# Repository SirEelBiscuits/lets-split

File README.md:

# lets-split

a custom remake of the lets split keyboard pcb

PCB designed to match [this case](https://mechboards.co.uk/shop/kits/lets-split-kit/#pcb).

Uses the QMK firmware, my fork of which is here: https://github.com/SirEelBiscuits/qmk_firmware/tree/garnet

As yet, keyboard and keymap are not merged upstream.

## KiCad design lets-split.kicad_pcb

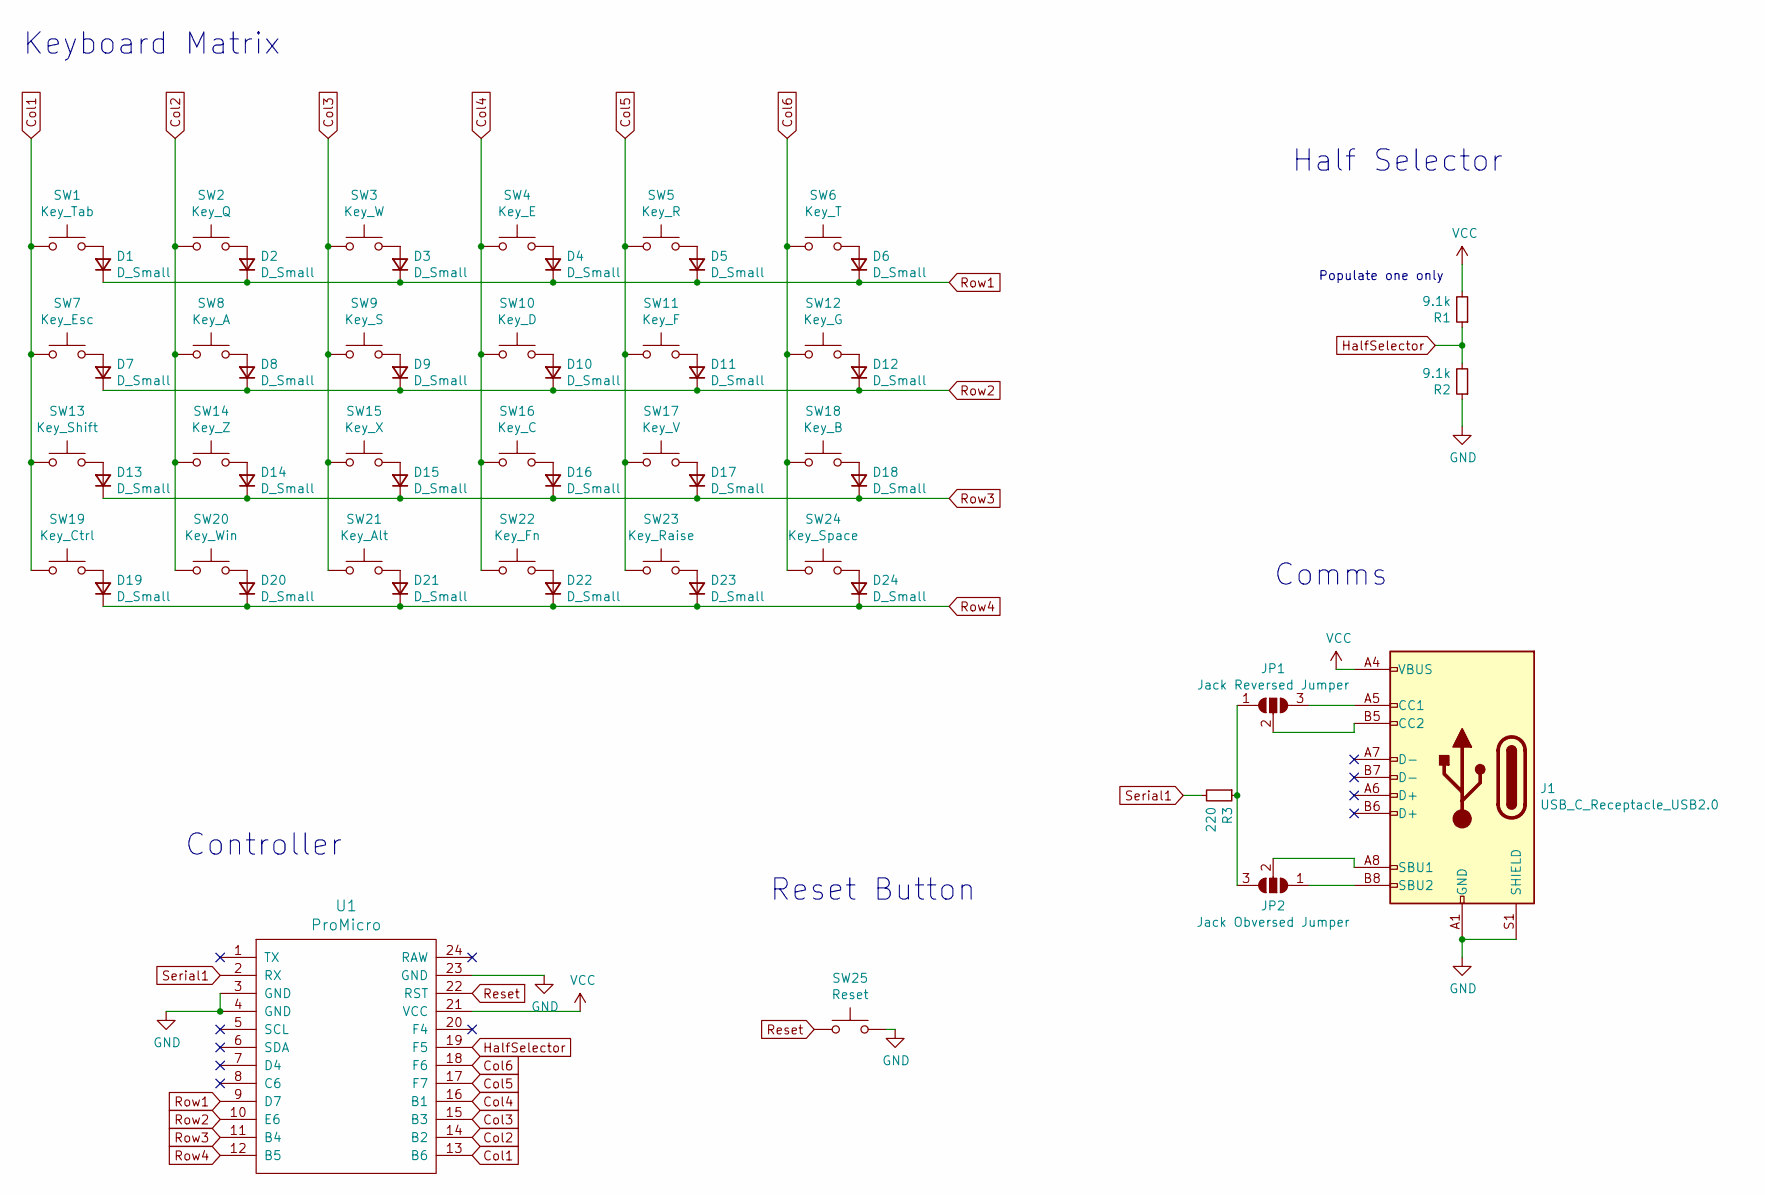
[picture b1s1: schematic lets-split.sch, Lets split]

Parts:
D1, D2, D3, D4, D5, D6, D7, D8, D9, D10, D11, D12, D13, D14, D15, D16, D17, D18, D19, D20, D21, D22, D23, D24: D_Small; D_DO-35_SOD27_P7.62mm_Horizontal
J1: USB_C_Receptacle_USB2.0; USB_C_GCT_USB4085
JP1: Jack Reversed Jumper; SolderJumper-3_P1.3mm_Open_RoundedPad1.0x1.5mm
JP2: Jack Obversed Jumper; SolderJumper-3_P1.3mm_Open_RoundedPad1.0x1.5mm
R1, R2: 9.1k; R_Axial_DIN0207_L6.3mm_D2.5mm_P7.62mm_Horizontal
R3: 220; R_Axial_DIN0207_L6.3mm_D2.5mm_P7.62mm_Horizontal
SW1: Key_Tab; SW_MX_reversible
SW2: Key_Q; SW_MX_reversible
SW3: Key_W; SW_MX_reversible
SW4: Key_E; SW_MX_reversible
SW5: Key_R; SW_MX_reversible
SW6: Key_T; SW_MX_reversible
SW7: Key_Esc; SW_MX_reversible
SW8: Key_A; SW_MX_reversible
SW9: Key_S; SW_MX_reversible
SW10: Key_D; SW_MX_reversible
SW11: Key_F; SW_MX_reversible
SW12: Key_G; SW_MX_reversible
SW13: Key_Shift; SW_MX_reversible
SW14: Key_Z; SW_MX_reversible
SW15: Key_X; SW_MX_reversible
SW16: Key_C; SW_MX_reversible
SW17: Key_V; SW_MX_reversible
SW18: Key_B; SW_MX_reversible
SW19: Key_Ctrl; SW_MX_reversible
SW20: Key_Win; SW_MX_reversible
SW21: Key_Alt; SW_MX_reversible
SW22: Key_Fn; SW_MX_reversible
SW23: Key_Raise; SW_MX_reversible
SW24: Key_Space; SW_MX_reversible
SW25: Reset; SW_PUSH_6mm_H4.3mm
U1: ProMicro

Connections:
Col1: SW1.1, SW7.1, SW13.1, SW19.1, U1.13 (B6)
Col2: SW2.1, SW8.1, SW14.1, SW20.1, U1.14 (B2)
Col3: SW3.1, SW9.1, SW15.1, SW21.1, U1.15 (B3)
Col4: SW4.1, SW10.1, SW16.1, SW22.1, U1.16 (B1)
Col5: SW5.1, SW11.1, SW17.1, SW23.1, U1.17 (F7)
Col6: SW6.1, SW12.1, SW18.1, SW24.1, U1.18 (F6)
GND: J1.A1 (GND), J1.A12 (GND), J1.B1 (GND), J1.B12 (GND), J1.S1 (SHIELD), R2.1, SW25.2, U1.3 (GND), U1.4 (GND), U1.23 (GND)
HalfSelector: R1.1, R2.2, U1.19 (F5)
unnamed: D1.2 (A), SW1.2
unnamed: D2.2 (A), SW2.2
unnamed: D3.2 (A), SW3.2
unnamed: D4.2 (A), SW4.2
unnamed: D5.2 (A), SW5.2
unnamed: D6.2 (A), SW6.2
unnamed: D7.2 (A), SW7.2
unnamed: D8.2 (A), SW8.2
unnamed: D9.2 (A), SW9.2
unnamed: D10.2 (A), SW10.2
unnamed: D11.2 (A), SW11.2
unnamed: D12.2 (A), SW12.2
unnamed: D13.2 (A), SW13.2
unnamed: D14.2 (A), SW14.2
unnamed: D15.2 (A), SW15.2
unnamed: D16.2 (A), SW16.2
unnamed: D17.2 (A), SW17.2
unnamed: D18.2 (A), SW18.2
unnamed: D19.2 (A), SW19.2
unnamed: D20.2 (A), SW20.2
unnamed: D21.2 (A), SW21.2
unnamed: D22.2 (A), SW22.2
unnamed: D23.2 (A), SW23.2
unnamed: D24.2 (A), SW24.2
unnamed: J1.A5 (CC1), JP1.3 (B)
unnamed: J1.A8 (SBU1), JP2.2 (C)
unnamed: J1.B5 (CC2), JP1.2 (C)
unnamed: J1.B8 (SBU2), JP2.1 (A)
unnamed: JP1.1 (A), JP2.3 (B), R3.1
Reset: SW25.1, U1.22 (RST)
Row1: D1.1 (K), D2.1 (K), D3.1 (K), D4.1 (K), D5.1 (K), D6.1 (K), U1.9 (D7)
Row2: D7.1 (K), D8.1 (K), D9.1 (K), D10.1 (K), D11.1 (K), D12.1 (K), U1.10 (E6)
Row3: D13.1 (K), D14.1 (K), D15.1 (K), D16.1 (K), D17.1 (K), D18.1 (K), U1.11 (B4)
Row4: D19.1 (K), D20.1 (K), D21.1 (K), D22.1 (K), D23.1 (K), D24.1 (K), U1.12 (B5)
Serial1: R3.2, U1.2 (RX)
VCC: J1.A4 (VBUS), J1.A9 (VBUS), J1.B4 (VBUS), J1.B9 (VBUS), R1.2, U1.21 (VCC)

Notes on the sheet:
Populate one only
Keyboard Matrix
Controller
Half Selector
Comms
Reset Button

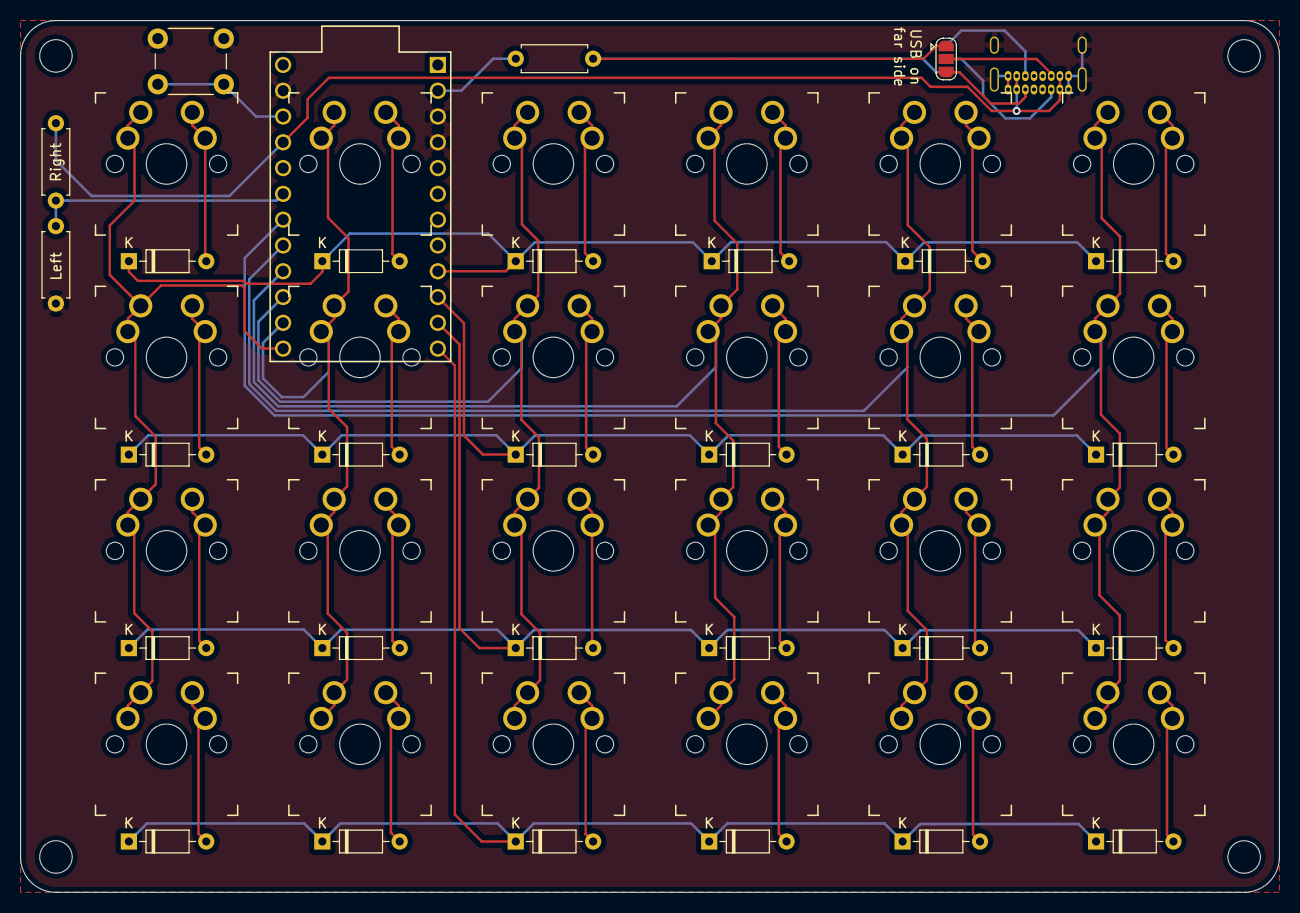
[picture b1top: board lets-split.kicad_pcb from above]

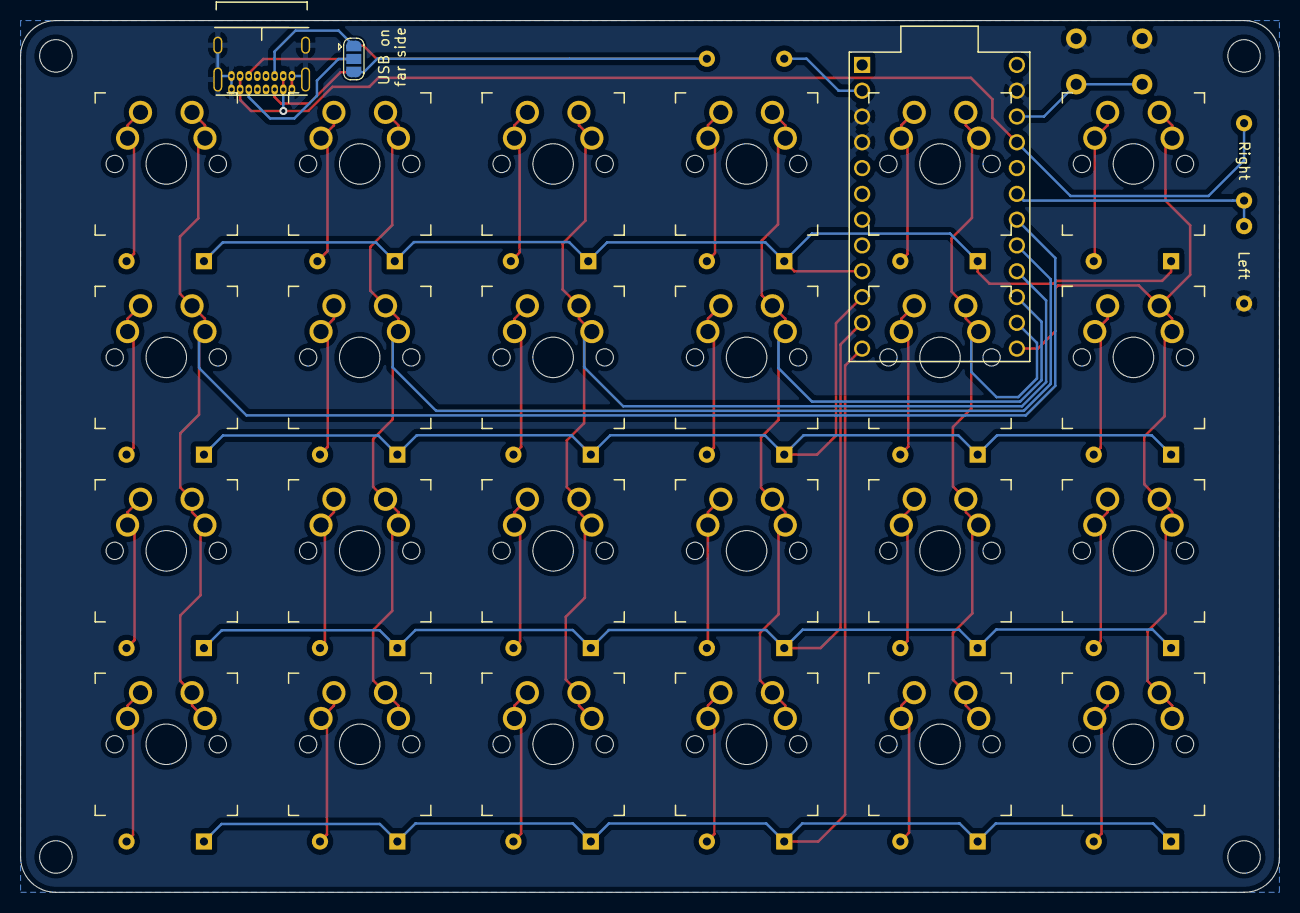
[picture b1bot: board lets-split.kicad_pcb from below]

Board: 2 copper layers, 124.0 x 85.9 mm, 56 parts (3 on the bottom side), 44 nets.

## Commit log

2021-06-12 added submodules
2021-06-12 kicad gitignore
2021-06-12 rev 1 of schematic started.
    All Keys
    TRRS
    Reset switch
    handedness jumper
2021-06-12 added annotations
2021-06-12 Assigned footprints to most components
2021-06-12 Switched TRRS to USB-C abuse. Should be safer.
    Also added resistor on data pins
    And replaced hand selector jumper with a pull up/down resistor (lower
    power I guess?)
2021-06-12 started notes file for parts
2021-06-12 added more notes
2021-06-12 Corrected footprint associations
2021-06-13 corrected reset button footprint
2021-06-13 Created PCB file, positioned parts
2021-06-13 Fixed USB-C connector not passing inspection.
    Added jumper to allow it to be mounted on either side of the board
2021-06-13 PCB traces laid. Fixed labels on columns on schematic.
2021-06-13 corrected reset button to go to gnd
2021-06-13 Added ground planes
2021-06-14 added screw holes, tweaked board edge positions
2021-06-14 Incorporated Kliment's feedback
    Moved traces apart from everything
    Removed one via
    moved vias from under USB connector
    Rounded corners
2021-06-14 added labels for jumpers and resistors
2021-06-14 Reversed column pin order to tidy PCB
2021-06-15 Revised board
    Moved controller over 1 column
    moved usb-c to top edge
    simplified routing overall
    now only 1 via, and absolute minimum number of traces under the USB jack
    (one each side!)
2021-07-03 Update README.md
    fixed mispasted link

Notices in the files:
lets-split.kicad_pcb:
licence: DWTFYW
